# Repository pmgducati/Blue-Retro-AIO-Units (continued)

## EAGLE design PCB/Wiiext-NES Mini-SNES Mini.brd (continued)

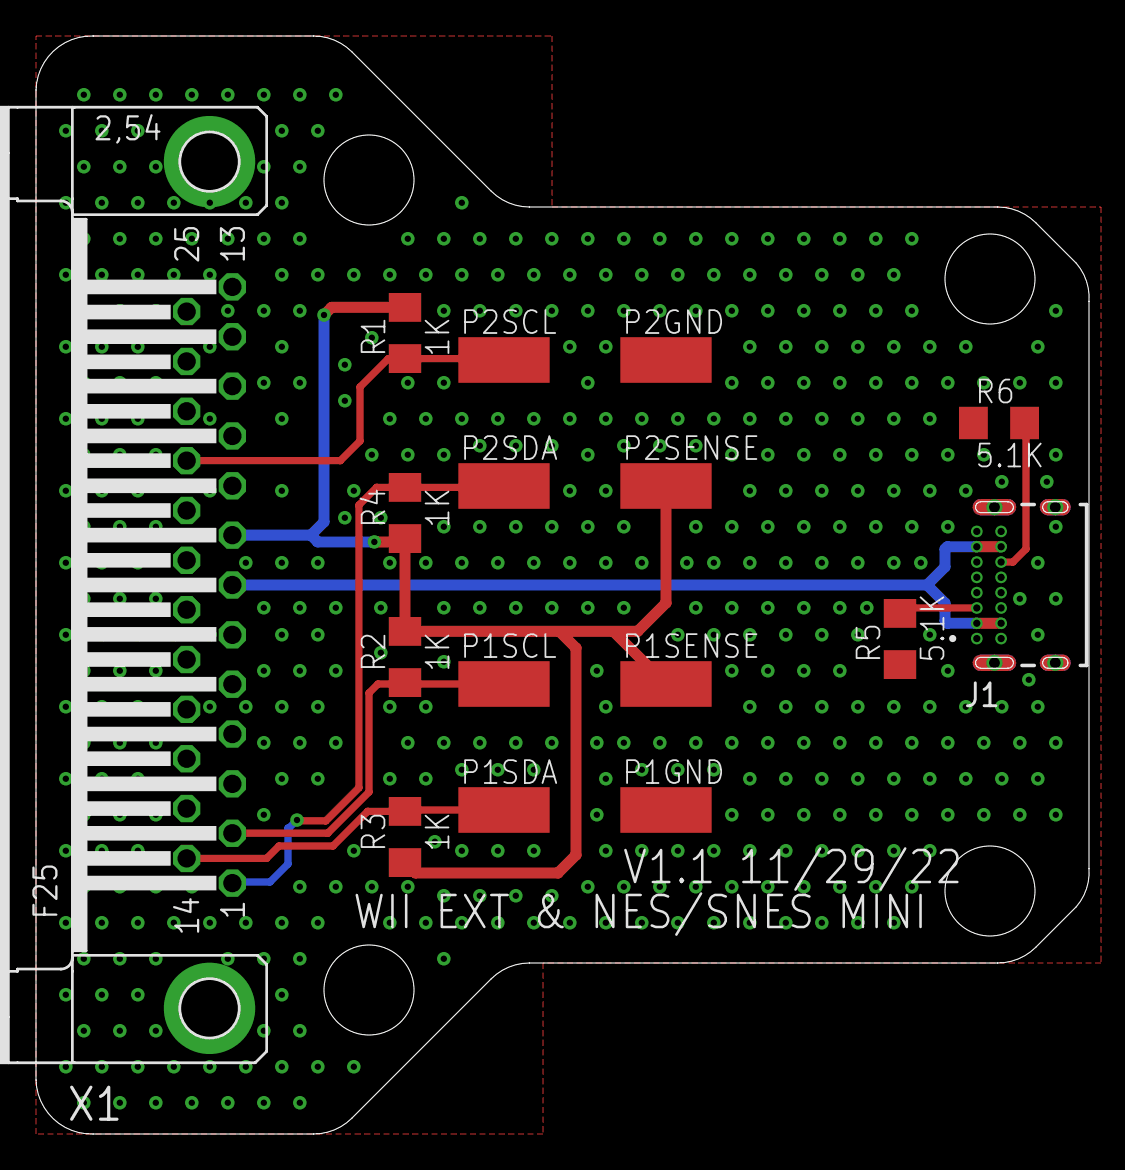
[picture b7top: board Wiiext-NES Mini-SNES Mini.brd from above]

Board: 2 copper layers, 58.5 x 61.0 mm, 16 parts (0 on the bottom side), 9 nets.
